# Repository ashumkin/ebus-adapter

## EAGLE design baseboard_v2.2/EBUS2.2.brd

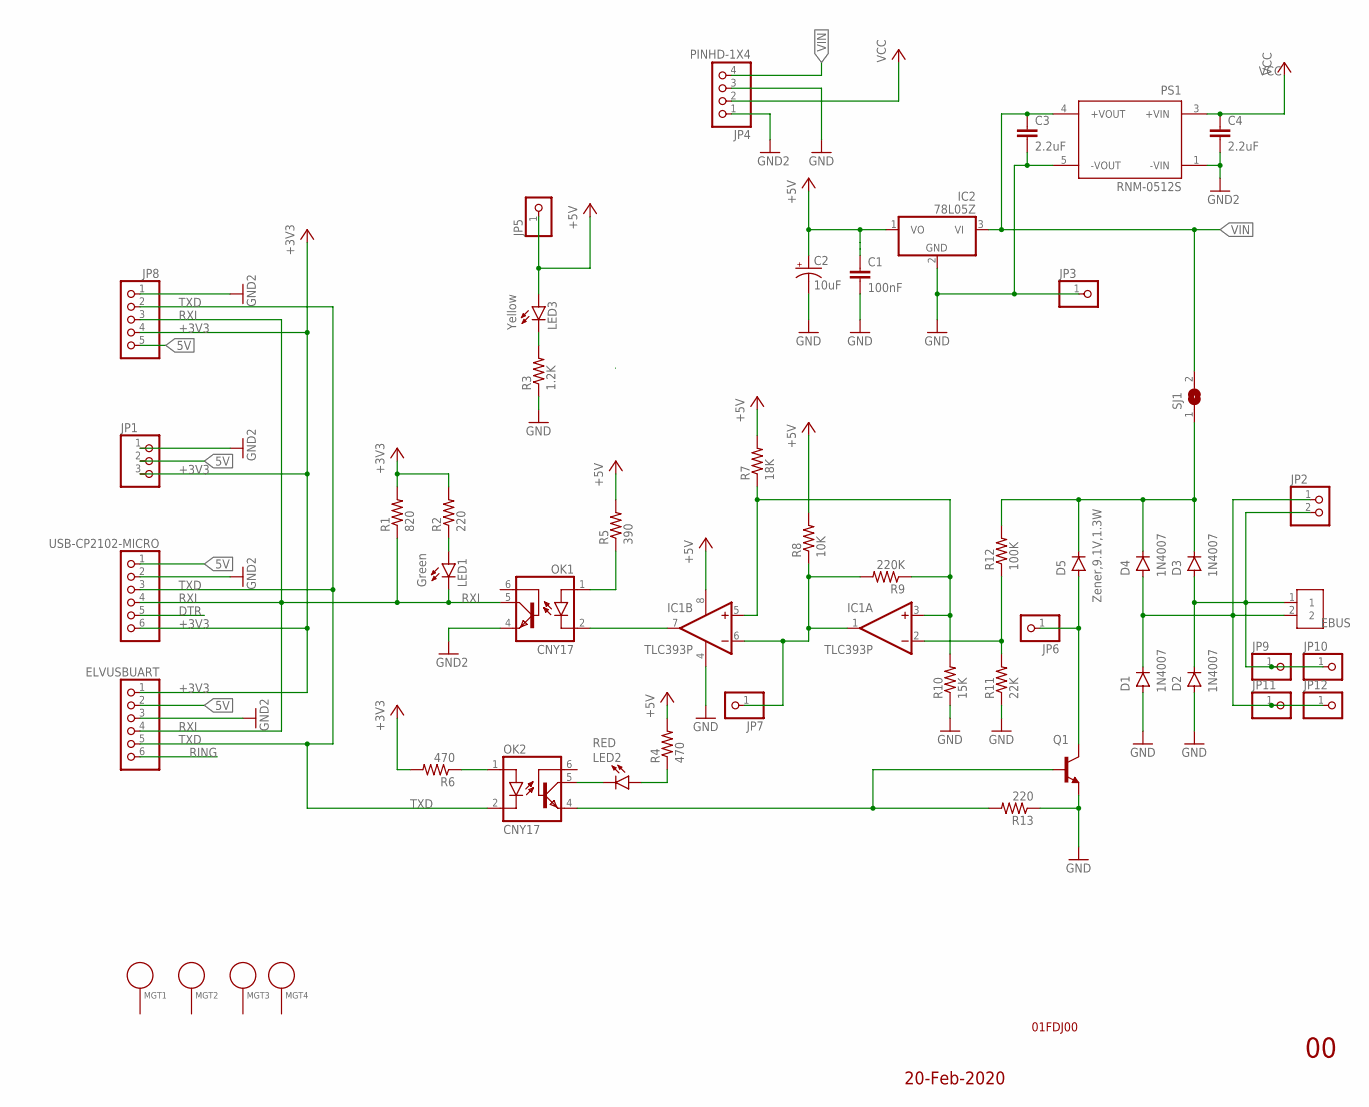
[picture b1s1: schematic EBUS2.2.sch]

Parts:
C1: 100nF; CAP-PTH-SMALL-KIT
C2: 10uF; CPOL-RADIAL-2.5MM-5MM-KIT
C3, C4: 2.2uF; CAP-PTH-SMALL-KIT
D1, D2, D3, D4: 1N4007; DO-41
D5: Zener,9.1V,1.3W; DO-41
EBUS: 2828XX-2282837-2; TERMBLK_508-2N
ELVUSBUART: PINHD-1X6; 1X06
IC1: TLC393P; DIL08
IC2: 78L05Z; TO92
JP1: PINHD-1X3; 1X03
JP2: PINHD-1X2; 1X02
JP3, JP5, JP6, JP7, JP9, JP10, JP11, JP12: PINHD-1X1; 1X01
JP4: PINHD-1X4; 1X04
JP8: PINHD-1X5; 1X05
LED1: Green; LED5MM
LED2: RED; LED5MM
LED3: Yellow; LED5MM
MGT1, MGT2, MGT3, MGT4: MOUNTING_HOLE; BEAGLEBONEBLACK_MOUNTING_HOLE
OK1, OK2: CNY17; DIL06
PS1: RNM-0512S; CONV_RNM-0512S
Q1: BC337-NPN-TO92-CBE; TO92-CBE
R1: 820; 0204/7
R2, R13: 220; 0204/7
R3: 1.2K; 0204/7
R4, R6: 470; 0204/7
R5: 390; 0204/7
R7: 18K; 0204/7
R8: 10K; 0204/7
R9: 220K; 0204/7
R10: 15K; 0204/7
R11: 22K; 0204/7
R12: 100K; 0204/7
SJ1: SJW
USB-CP2102-MICRO: PINHD-1X6; 1X06

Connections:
5V: ELVUSBUART.2, JP1.2, JP8.5, USB-CP2102-MICRO.1
+3V3: ELVUSBUART.1, JP1.3, JP8.4, R1.2, R2.2, R6.2, USB-CP2102-MICRO.6
+5V: C1.1, C2.1 (+), IC1.8 (V+), IC2.1 (VO), JP5.1, LED3.A, R4.2, R5.2, R7.2, R8.2
DTR: USB-CP2102-MICRO.5
GND: C1.2, C2.2 (-), C3.2, C4.2, D1.A, D2.A, ELVUSBUART.3, IC1.4 (V-), IC2.2 (GND), JP1.1, JP3.1, JP4.1, JP4.3, JP8.1, OK1.4 (EMI), PS1.1 (-VIN), PS1.5 (-VOUT), Q1.E, R3.1, R10.1, R11.1, R13.1, USB-CP2102-MICRO.2
unnamed: LED3.K (C), R3.2
unnamed: LED1.A, R2.1
unnamed: LED2.A, R4.1
unnamed: IC1.7 (OUT), OK1.2 (C)
unnamed: OK1.1 (A), R5.1
unnamed: IC1.2 (-IN), R11.2, R12.1
unnamed: OK2.1 (A), R6.1
unnamed: IC1.1 (OUT), IC1.6 (-IN), JP7.1, R8.1, R9.2
unnamed: IC1.3 (+IN), IC1.5 (+IN), R7.1, R9.1, R10.2
unnamed: D3.C, D4.C, D5.C, R12.2, SJ1.1
unnamed: LED2.K (C), OK2.5 (COL)
unnamed: D5.A, JP6.1, Q1.C
unnamed: D2.C, D3.A, EBUS.1, JP2.2, JP9.1, JP10.1
unnamed: D1.C, D4.A, EBUS.2, JP2.1, JP11.1, JP12.1
unnamed: OK2.4 (EMI), Q1.B, R13.2
RING: ELVUSBUART.6
RXI: ELVUSBUART.4, JP8.3, LED1.K (C), OK1.5 (COL), R1.1, USB-CP2102-MICRO.4
TXD: ELVUSBUART.5, JP8.2, OK2.2 (C), USB-CP2102-MICRO.3
VCC: C4.1, JP4.2, PS1.3 (+VIN)
VIN: C3.1, IC2.3 (VI), JP4.4, PS1.4 (+VOUT), SJ1.2

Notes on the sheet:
20-Feb-2020
01FDJ00

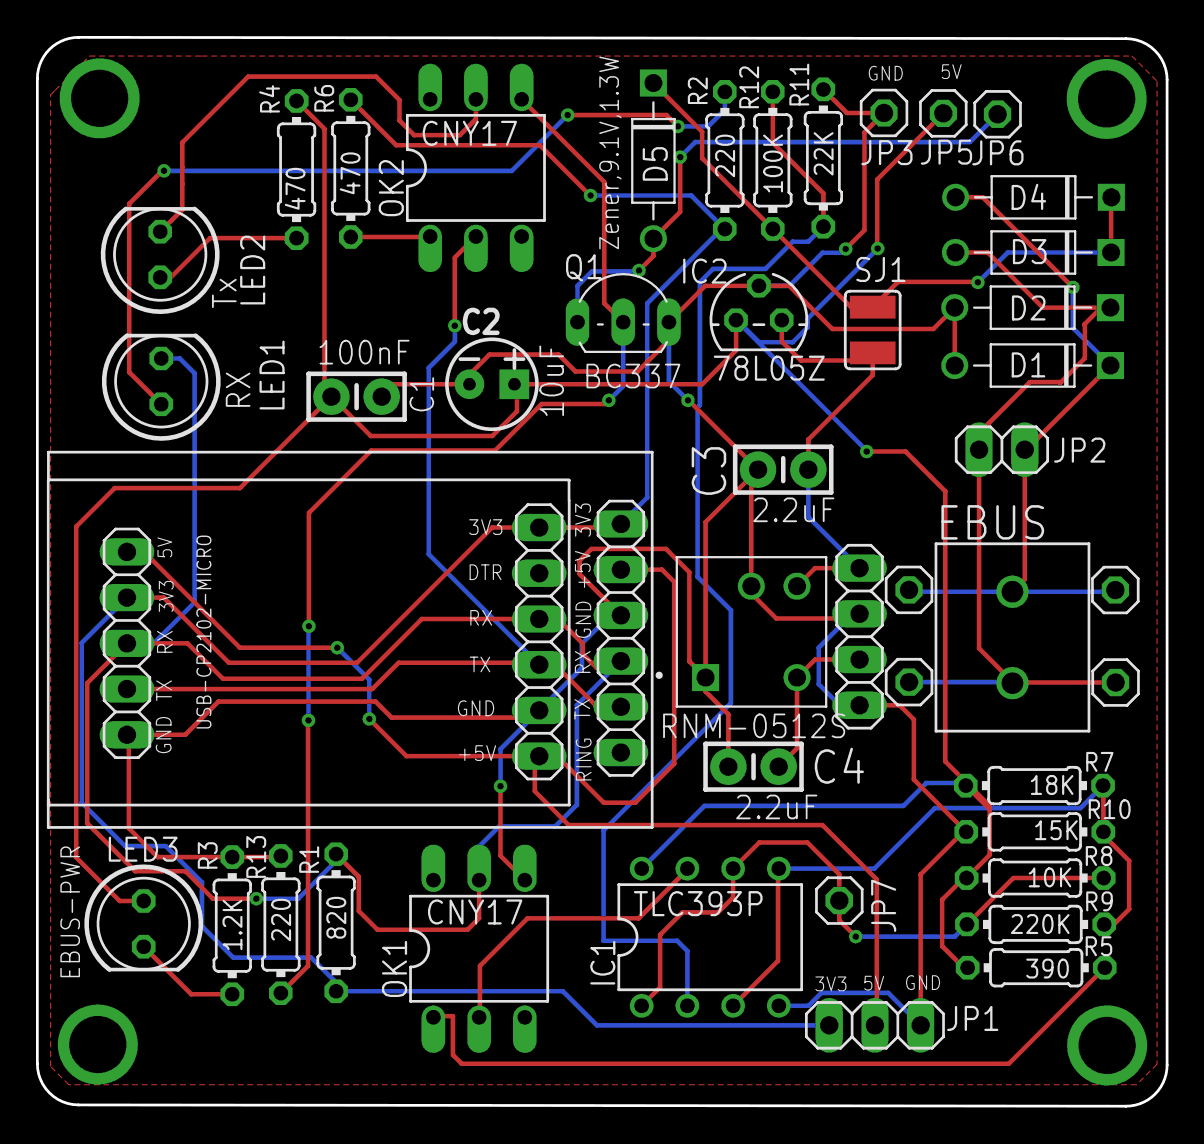
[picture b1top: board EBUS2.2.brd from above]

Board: 2 copper layers, 62.8 x 59.4 mm, 51 parts (0 on the bottom side), 23 nets.

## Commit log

2021-04-28 change external power pinout
2021-04-29 Fix TLC389P powering

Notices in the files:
parts and their libraries:
SparkFun-Capacitors: Licensing: Creative Commons ShareAlike 4.0 International - https://creativecommons.org/licenses/by-sa/4.0
